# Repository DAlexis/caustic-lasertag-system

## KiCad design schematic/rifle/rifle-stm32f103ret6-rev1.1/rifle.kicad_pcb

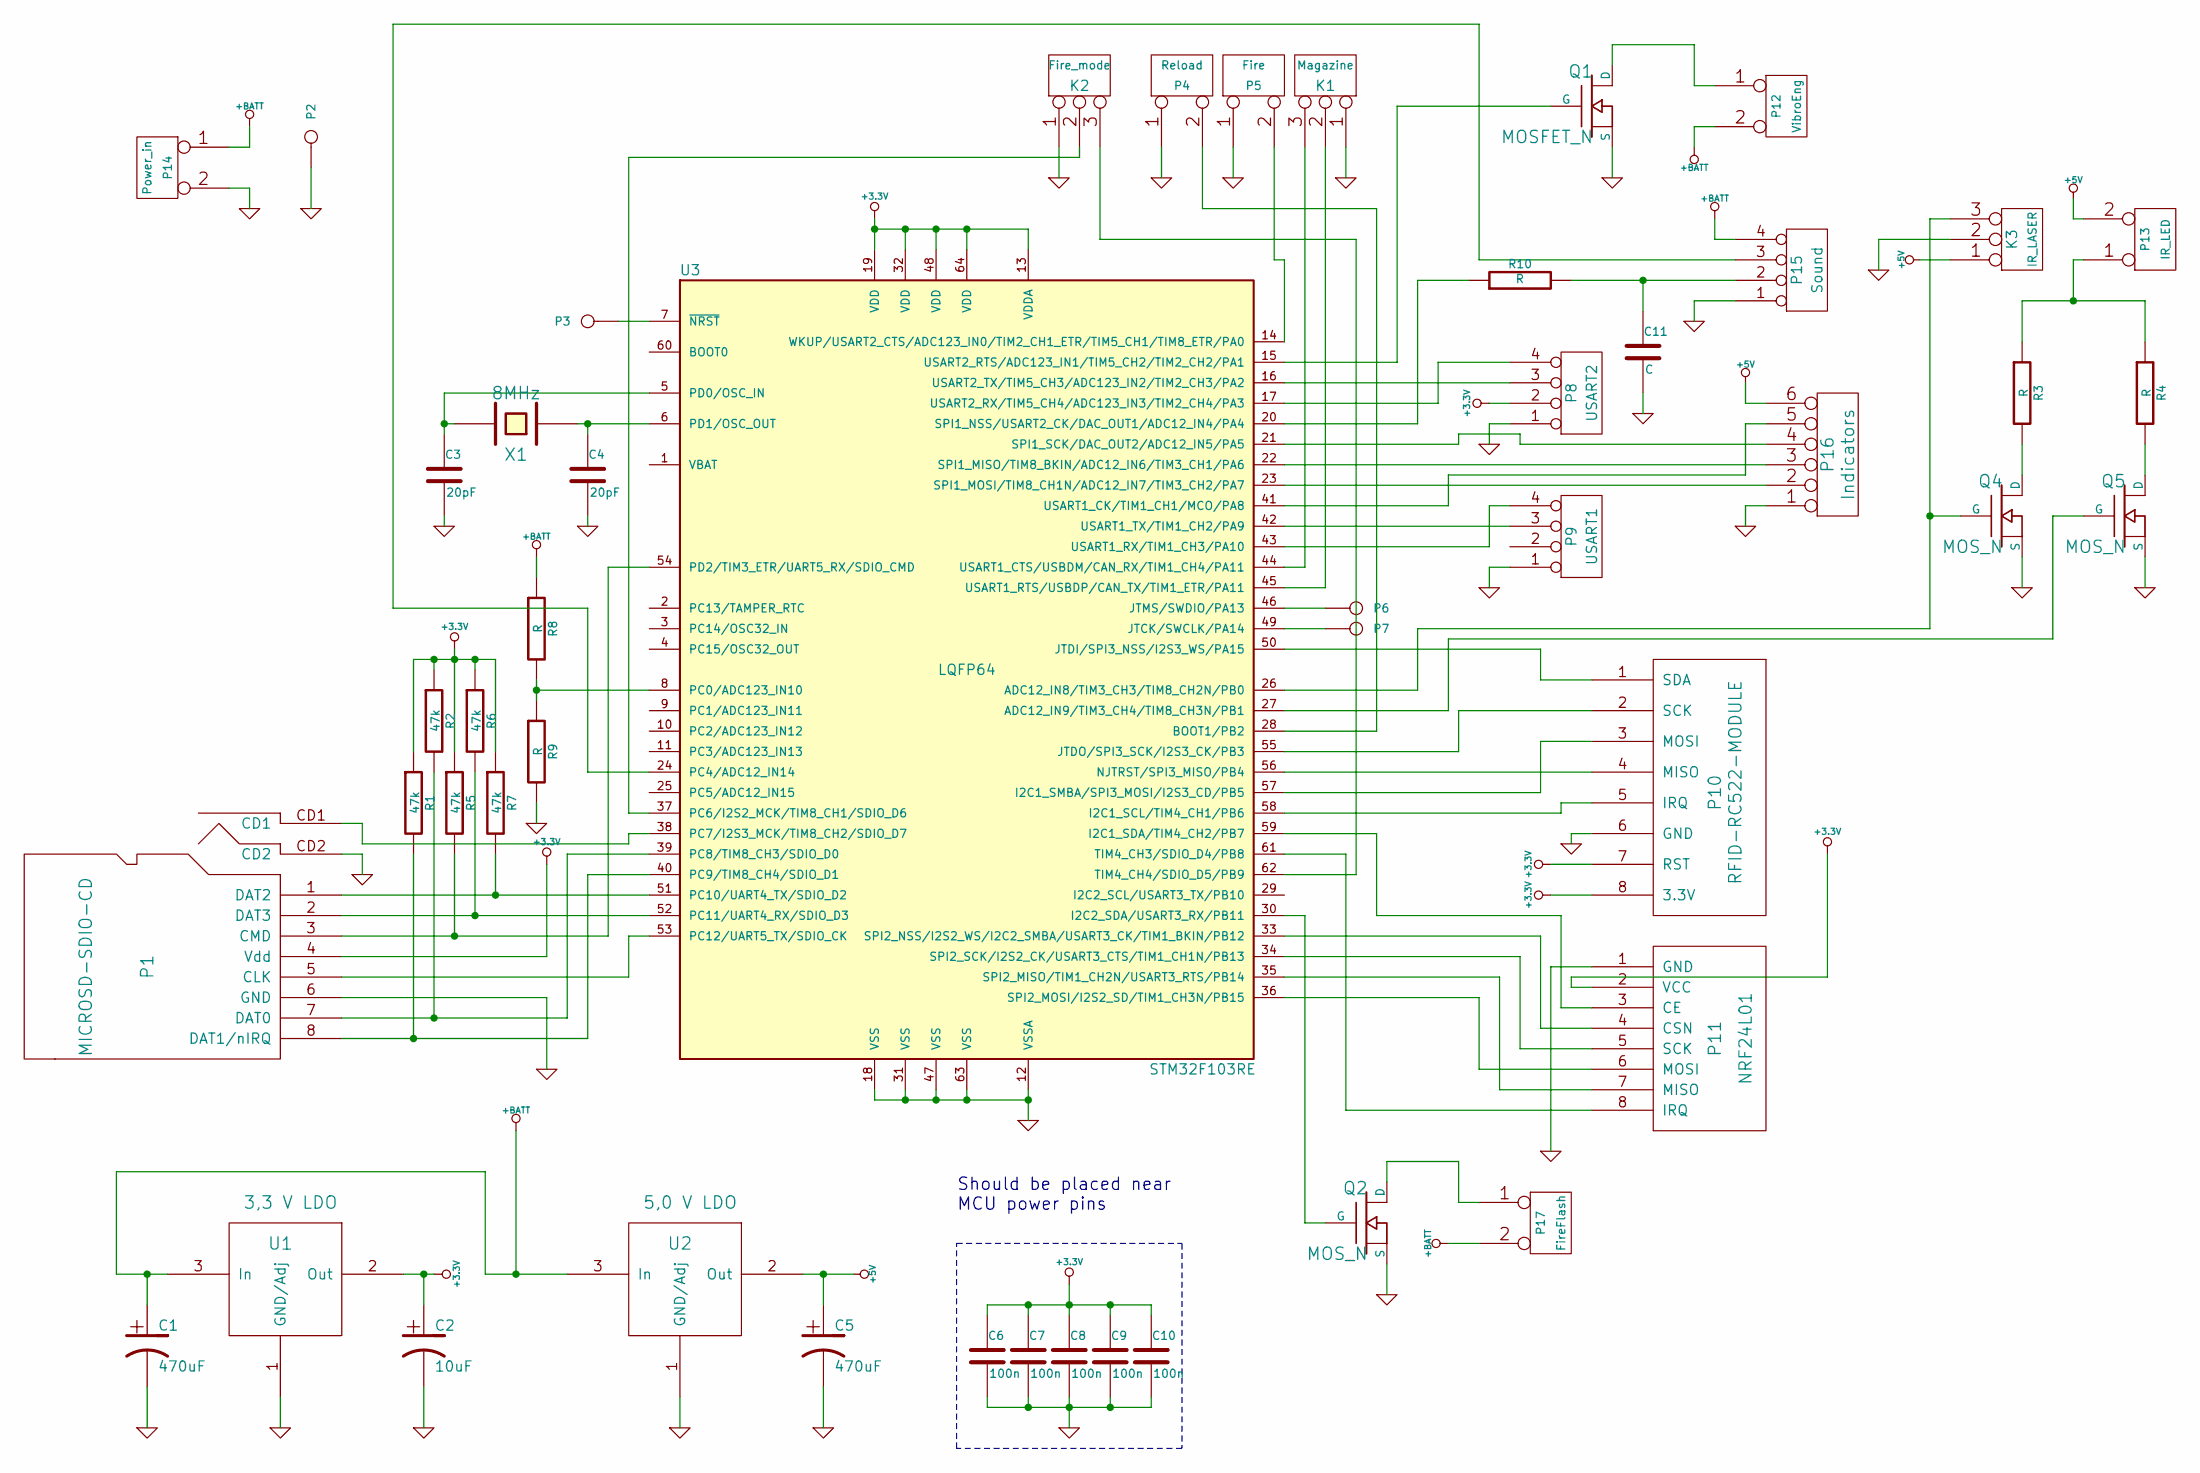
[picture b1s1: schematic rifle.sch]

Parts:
C1, C5: 470uF
C2: 10uF
C3, C4: 20pF
C6, C7, C8, C9, C10: 100n
C11: C
K1: Magazine
K2: Fire_mode
K3: IR_LASER
P1: MICROSD-SDIO-CD
P2: GND
P3: Reset
P4: Reload
P5: Fire
P6: SWD_IO
P7: SWD_CLK
P8: USART2
P9: USART1
P10: RFID-RC522-MODULE
P11: NRF24L01
P12: VibroEng
P13: IR_LED
P14: Power_in
P15: Sound
P16: Indicators
P17: FireFlash
Q1: MOSFET_N
Q2, Q4, Q5: MOS_N
R1, R2, R5, R6, R7: 47k
R3, R4, R8, R9, R10: R
U1: 3,3 V LDO
U2: 5,0 V LDO
U3: STM32F103RE; LQFP64
X1: 8MHz

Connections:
+3.3V: C2.1, C6.1, C7.1, C8.1, C9.1, C10.1, P1.4 (Vdd), P8.2, P10.7 (RST), P10.8 (3.3V), P11.2 (VCC), R1.1, R2.1, R5.1, R6.1, R7.1, U1.2 (Out), U3.13 (VDDA), U3.19 (VDD), U3.32 (VDD), U3.48 (VDD), U3.64 (VDD)
+5V: C5.1, K3.1, P13.2 (PM), P16.6, U2.2 (Out)
+BATT: C1.1, P12.2 (PM), P14.1, P15.4, P17.2 (PM), R8.1, U1.3 (In), U2.3 (In)
GND: C1.2, C2.2, C3.2, C4.2, C5.2, C6.2, C7.2, C8.2, C9.2, C10.2, C11.2, K1.1, K2.1, K3.2 (PM), P1.6 (GND), P1.CD2, P2.1, P4.1, P5.1, P8.1, P9.1, P10.6 (GND), P11.1 (GND), P14.2 (PM), P15.1, P16.1, Q1.S, Q2.S, Q4.S, Q5.S, R9.2, U1.1 (GND/Adj), U2.1 (GND/Adj), U3.12 (VSSA), U3.18 (VSS), U3.31 (VSS), U3.47 (VSS), U3.63 (VSS)
unnamed: Q4.D, R3.2
unnamed: Q5.D, R4.2
unnamed: K3.3, Q4.G, U3.26 (ADC12_IN8/TIM3_CH3/TIM8_CH2N/PB0)
unnamed: Q5.G, U3.27 (ADC12_IN9/TIM3_CH4/TIM8_CH3N/PB1)
unnamed: P11.4 (CSN), U3.33 (SPI2_NSS/I2S2_WS/I2C2_SMBA/USART3_CK/TI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)
unnamed: P11.6 (MOSI), U3.36 (SPI2_MOSI/I2S2_SD/TIM1_CH3N/PB15)
unnamed: P11.7 (MISO), U3.35 (SPI2_MISO/TIM1_CH2N/USART3_RTS/PB14)
unnamed: P11.5 (SCK), U3.34 (SPI2_SCK/I2S2_CK/USART3_CTS/TIM1_CH1N/P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)
unnamed: P11.8 (IRQ), U3.61 (TIM4_CH3/SDIO_D4/PB8)
unnamed: P11.3 (CE), U3.59 (I2C1_SDA/TIM4_CH2/PB7)
unnamed: Q1.G, U3.15 (USART2_RTS/ADC123_IN1/TIM5_CH2/TIM2_CH2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)
unnamed: K1.3, U3.44 (USART1_CTS/USBDM/CAN_RX/TIM1_CH4/PA11)
unnamed: K1.2 (PM), U3.45 (USART1_RTS/USBDP/CAN_TX/TIM1_ETR/PA11)
unnamed: P1.5 (CLK), U3.53 (PC12/UART5_TX/SDIO_CK)
unnamed: C4.1, U3.6 (PD1/OSC_OUT), X1.1
unnamed: C3.1, U3.5 (PD0/OSC_IN), X1.2
unnamed: P10.1 (SDA), U3.50 (JTDI/SPI3_NSS/I2S3_WS/PA15)
unnamed: P8.4, U3.17 (USART2_RX/TIM5_CH4/ADC123_IN3/TIM2_CH4/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)
unnamed: P10.4 (MISO), U3.56 (NJTRST/SPI3_MISO/PB4)
unnamed: P10.3 (MOSI), U3.57 (I2C1_SMBA/SPI3_MOSI/I2S3_CD/PB5)
unnamed: P10.5 (IRQ), U3.58 (I2C1_SCL/TIM4_CH1/PB6)
unnamed: P3.1, U3.7 (~NRST)
unnamed: P6.1, U3.46 (JTMS/SWDIO/PA13)
unnamed: P7.1, U3.49 (JTCK/SWCLK/PA14)
unnamed: P9.3, U3.42 (USART1_TX/TIM1_CH2/PA9)
unnamed: P9.4, U3.43 (USART1_RX/TIM1_CH3/PA10)
unnamed: P8.3, U3.16 (USART2_TX/TIM5_CH3/ADC123_IN2/TIM2_CH3/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)
unnamed: P4.2 (PM), U3.28 (BOOT1/PB2)
unnamed: P5.2 (PM), U3.14 (WKUP/USART2_CTS/ADC123_IN0/TIM2_CH1_ETR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)
unnamed: P1.CD1, U3.38 (PC7/I2S3_MCK/TIM8_CH2/SDIO_D7)
unnamed: P1.2 (DAT3), R6.2, U3.52 (PC11/UART4_RX/SDIO_D3)
unnamed: P1.1 (DAT2), R7.2, U3.51 (PC10/UART4_TX/SDIO_D2)
unnamed: K2.2 (PM), U3.37 (PC6/I2S2_MCK/TIM8_CH1/SDIO_D6)
unnamed: R10.1, U3.20 (SPI1_NSS/USART2_CK/DAC_OUT1/ADC12_IN4/P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)
unnamed: P13.1, R3.1, R4.1
unnamed: P17.1, Q2.D
unnamed: Q2.G, U3.30 (I2C2_SDA/USART3_RX/PB11)
unnamed: C11.1, P15.2, R10.2
unnamed: P15.3, U3.24 (PC4/ADC12_IN14)
unnamed: P16.2, U3.23 (SPI1_MOSI/TIM8_CH1N/ADC12_IN7/TIM3_CH2/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)
unnamed: P16.3, U3.22 (SPI1_MISO/TIM8_BKIN/ADC12_IN6/TIM3_CH1/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)
unnamed: P16.4, U3.21 (SPI1_SCK/DAC_OUT2/ADC12_IN5/PA5)
unnamed: P12.1, Q1.D
unnamed: K2.3, U3.62 (TIM4_CH4/SDIO_D5/PB9)
unnamed: P10.2 (SCK), U3.55 (JTDO/SPI3_SCK/I2S3_CK/PB3)
unnamed: P1.8 (DAT1/nIRQ), R1.2, U3.40 (PC9/TIM8_CH4/SDIO_D1)
unnamed: P1.7 (DAT0), R2.2, U3.39 (PC8/TIM8_CH3/SDIO_D0)
unnamed: P1.3 (CMD), R5.2, U3.54 (PD2/TIM3_ETR/UART5_RX/SDIO_CMD)
unnamed: P16.5, U3.41 (USART1_CK/TIM1_CH1/MCO/PA8)
unnamed: R8.2, R9.1, U3.8 (PC0/ADC123_IN10)

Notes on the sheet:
Should be placed near MCU power pins

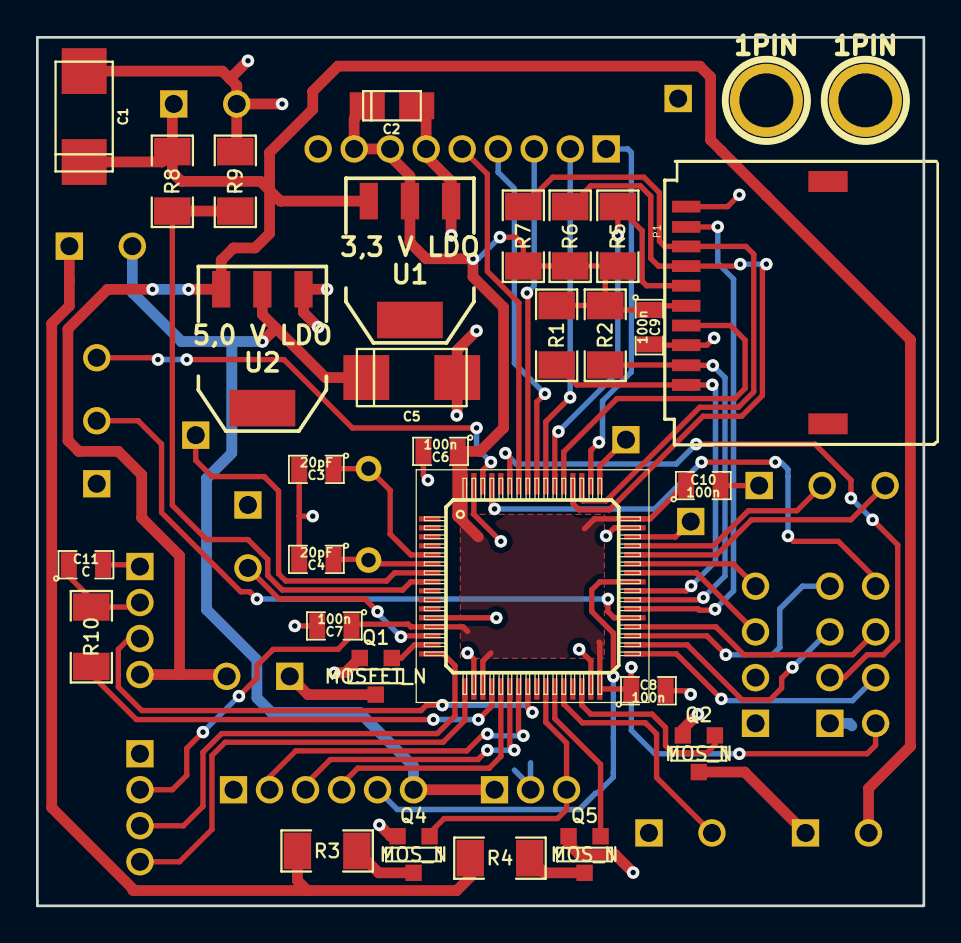
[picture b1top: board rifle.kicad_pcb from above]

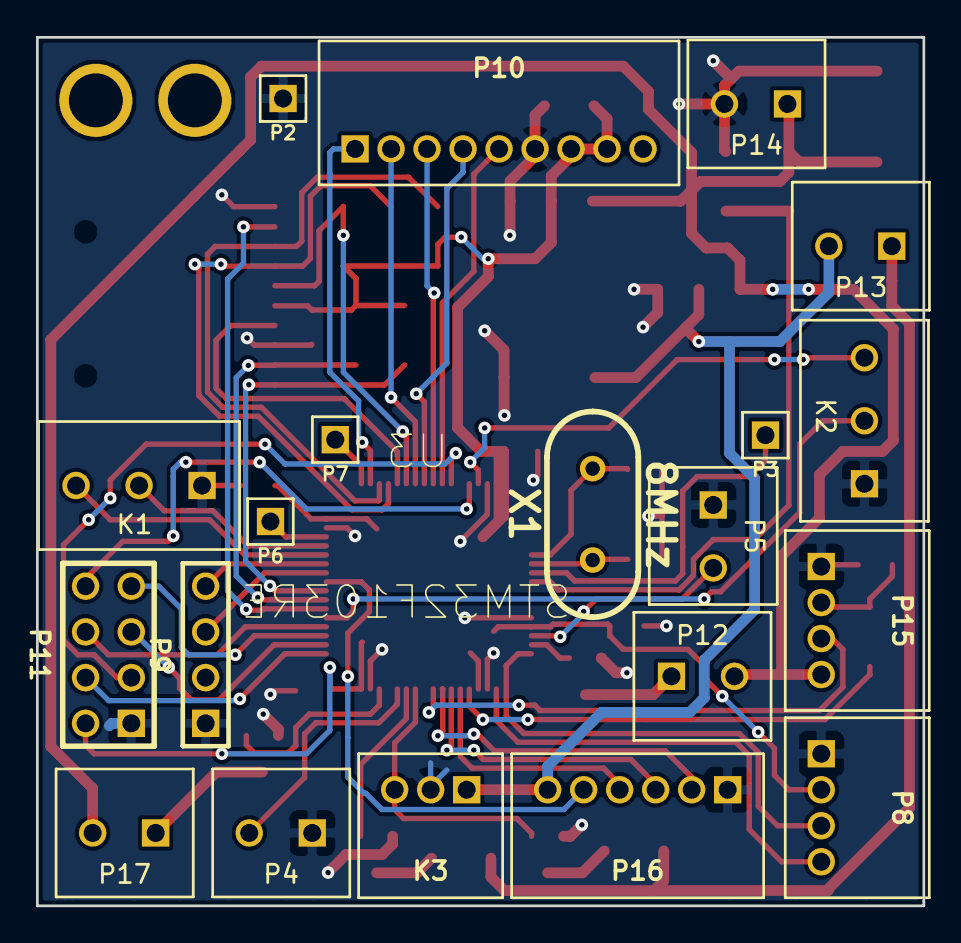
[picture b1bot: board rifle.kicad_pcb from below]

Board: 2 copper layers, 49.2 x 48.2 mm, 51 parts (20 on the bottom side), 54 nets.

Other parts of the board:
1PIN, 1PIN#2: P***; 1pin

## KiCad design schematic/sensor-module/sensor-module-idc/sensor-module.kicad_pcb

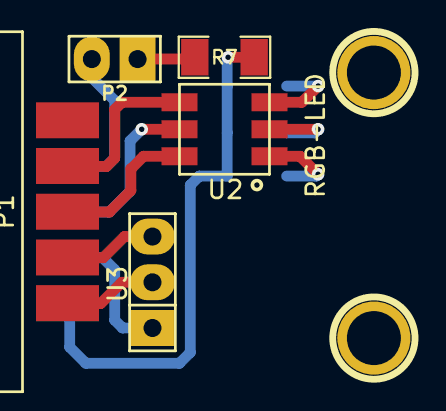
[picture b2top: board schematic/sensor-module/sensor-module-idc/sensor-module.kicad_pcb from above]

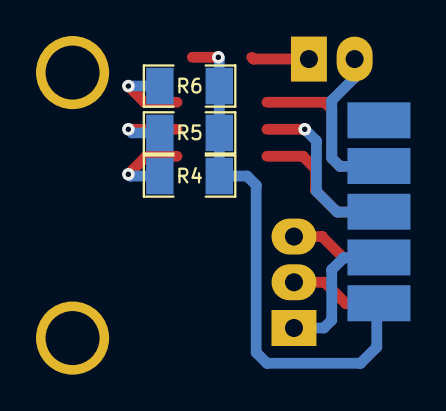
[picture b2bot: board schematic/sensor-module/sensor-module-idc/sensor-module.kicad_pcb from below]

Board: 2 copper layers, 8 parts (3 on the bottom side), 12 nets.

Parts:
P1: SENSOR_CONNECTOR; Sensors-connector-10x
P2: VibroEngine; PIN_ARRAY_LARGE_PADS_2.54mm_2X1
R4, R5, R6, R7: R; SM1206
U2: RGB-LED; RGB-led
U3: TSOP4856; PIN_ARRAY_LARGE_PADS_2.54mm_3X1

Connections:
+3.3V: P1.3, U3.3
+BATT: P1.2, R4.1, R5.1, R6.1, R7.2
GND: P1.1, U3.2
unnamed: P1.4, U3.1
unnamed: R6.2, U2.6
unnamed: R5.2, U2.5
unnamed: R4.2, U2.4
unnamed: P1.8, P2.2
unnamed: P2.1, R7.1
unnamed: P1.5, U2.3
unnamed: P1.6, U2.2
unnamed: P1.7, U2.1

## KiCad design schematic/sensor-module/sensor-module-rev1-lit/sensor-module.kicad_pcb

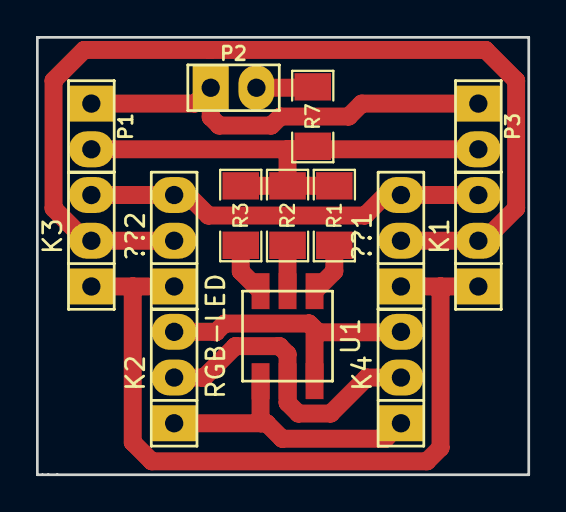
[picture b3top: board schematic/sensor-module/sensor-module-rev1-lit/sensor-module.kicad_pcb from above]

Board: 2 copper layers, 27.3 x 24.3 mm, 14 parts (0 on the bottom side), 12 nets.

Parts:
??1, ??2: TSOP4856; PIN_ARRAY_LARGE_PADS_2.54mm_3X1
K1, K3: SENSORS; PIN_ARRAY_LARGE_PADS_2.54mm_3X1
K2, K4: LEDs; PIN_ARRAY_LARGE_PADS_2.54mm_3X1
P1, P3: Vibro; PIN_ARRAY_LARGE_PADS_2.54mm_2X1
P2: VibroEngine; PIN_ARRAY_LARGE_PADS_2.54mm_2X1
R1, R2, R3, R7: R; SM1206
U1: RGB-LED; RGB-led

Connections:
+3.3V: ??1.3, ??2.3, K1.3, K3.3
+BATT: P1.2, P3.2, R1.1, R2.1, R3.1, R7.2
GND: ??1.2, ??2.2, K1.2, K3.2
unnamed: K2.1, K4.1, U1.1
unnamed: R1.2, U1.4
unnamed: R2.2, U1.5
unnamed: R3.2, U1.6
unnamed: K2.2, K4.2, U1.2
unnamed: ??1.1, ??2.1, K1.1, K3.1
unnamed: P2.2, R7.1
unnamed: P1.1, P2.1, P3.1
unnamed: K2.3, K4.3, U1.3

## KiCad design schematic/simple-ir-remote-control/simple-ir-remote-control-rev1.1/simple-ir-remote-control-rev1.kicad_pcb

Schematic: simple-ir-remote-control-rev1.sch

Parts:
C1, C2: CP1
C3, C4, C5, C6, C7, C8: C
K1: CONN_3
P1, P2, P3, P4: CONN_1
P5: CONN_5
P6: CONN_4
P7: CONN_5X2
P8: CONN_10
P9: CONN_2
Q1: MOSFET_N
R1, R2: R
U1: LINSTAB-(1-GND/ADJ,2-OUT,3-IN)
U2: STM32F100CB; LQFP48
X1: CRYSTAL

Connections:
+3.3V: C2.1, C5.1, C6.1, C7.1, C8.1, K1.1, U1.2 (Out), U2.9 (VDDA), U2.24 (VDD), U2.36 (VDD), U2.48 (VDD)
+BATT: C1.1, P9.2 (PM), U1.3 (In)
GND: C1.2, C2.2, C3.1, C4.1, C5.2, C6.2, C7.2, C8.2, P4.1, P6.1, P7.1, P7.2, P7.3, P7.4, P7.5, P7.6, P7.7, P7.8, P7.9, P7.10, P9.1, Q1.S, U1.1 (GND/Adj), U2.8 (VSSA), U2.23 (VSS), U2.35 (VSS), U2.47 (VSS)
unnamed: P8.1, U2.12 (USART2_TX/ADC1_IN2/TIM2_CH3/TIM15_CH1/P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)
unnamed: P5.1, U2.43 (PB7/I2C1_SDA/TIM17_CH1N/TIM4_CH2)
unnamed: P5.2, U2.42 (PB6/I2C1_SCL/TIM4_CH1/TIM16_CH1N)
unnamed: P5.3, U2.41 (PB5/I2C1_SMBA/TIM16_BKIN)
unnamed: P5.4, U2.40 (PB4/NJRST)
unnamed: P5.5, U2.39 (PB3/JTDO)
unnamed: P6.4, U2.31 (USART1_RX/TIM1_CH3/TIM17_BKIN/PA10)
unnamed: P6.3, U2.30 (USART1_TX/TIM1_CH2/TIM15_BKIN/PA9)
unnamed: P8.6, U2.17 (SPI1_MOSI/ADC1_IN7/TIM3_CH2/PA7)
unnamed: P8.8, U2.19 (PB1/ADC1_IN9/TIM3_CH4)
unnamed: P8.5, U2.16 (SPI1_MISO/ADC1_IN6/TIM3_CH1/PA6)
unnamed: P8.4, U2.15 (SPI1_SCK/ADC1_IN5/DAC2_OUT/PA5)
unnamed: P8.3, U2.14 (SPI1_NSS/ADC1_IN4/USART2_CK/DAC1_OUT/PA4)
unnamed: P8.2, U2.13 (USART2_RX/ADC1_IN3/TIM2_CH4/TIM15_CH2/P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)
unnamed: Q1.G, U2.11 (USART2_RTS/ADC1_IN1/TIM2_CH2/PA1)
unnamed: P1.1, U2.7 (~NRST)
unnamed: P2.1, U2.34 (JTMS/SWDIO/PA13)
unnamed: P3.1, U2.37 (JTCK/SWCLK/PA14)
unnamed: K1.3, R1.1
unnamed: K1.2 (PM), R2.1
unnamed: Q1.D, R1.2, R2.2
unnamed: P8.10, U2.21 (PB10/I2C2_SCL/USART3_TX)
unnamed: P8.9, U2.20 (PB2/BOOT1)
unnamed: P8.7, U2.18 (PB0/ADC1_IN8/TIM3_CH3)
unnamed: C4.2, U2.6 (OSC_OUT), X1.2
unnamed: C3.2, U2.5 (OSC_IN), X1.1

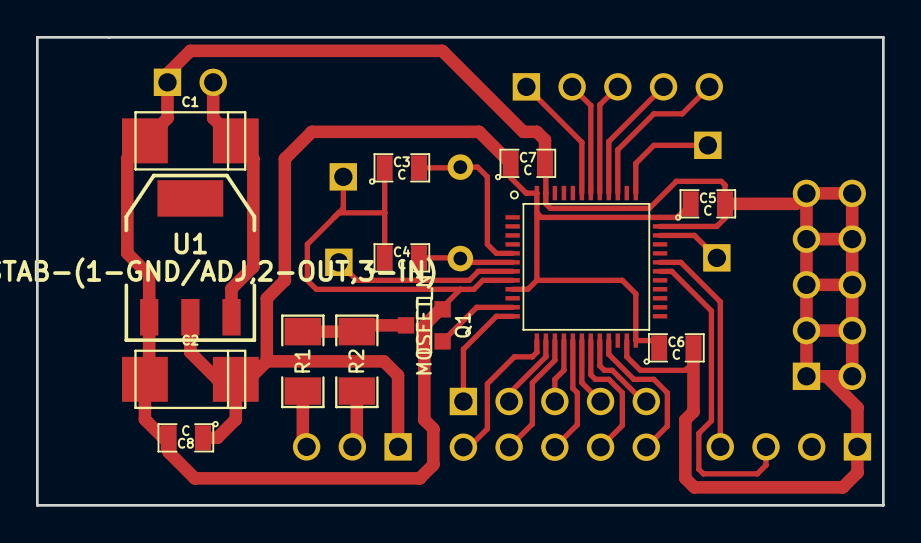
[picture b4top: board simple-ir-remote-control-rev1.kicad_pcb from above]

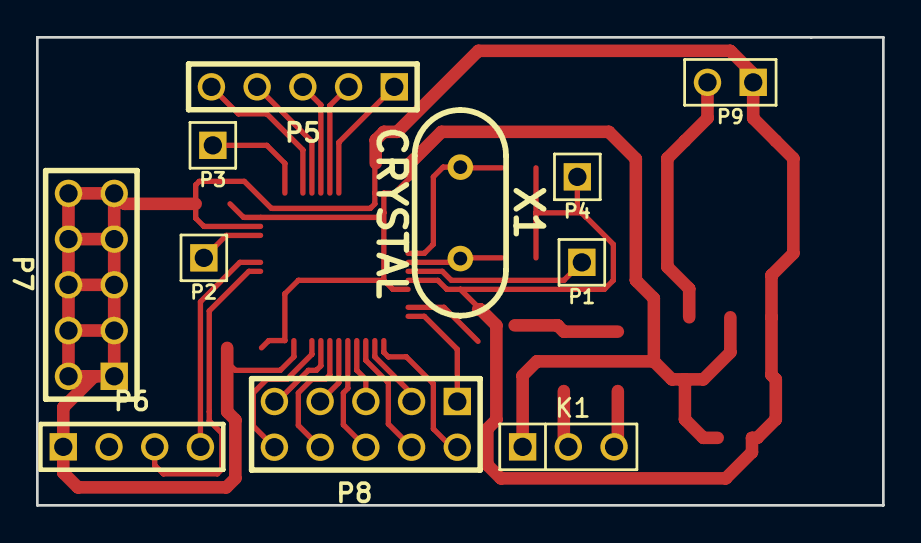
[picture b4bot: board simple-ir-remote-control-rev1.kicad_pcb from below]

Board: 2 copper layers, 47.0 x 26.0 mm, 24 parts (11 on the bottom side), 29 nets.
